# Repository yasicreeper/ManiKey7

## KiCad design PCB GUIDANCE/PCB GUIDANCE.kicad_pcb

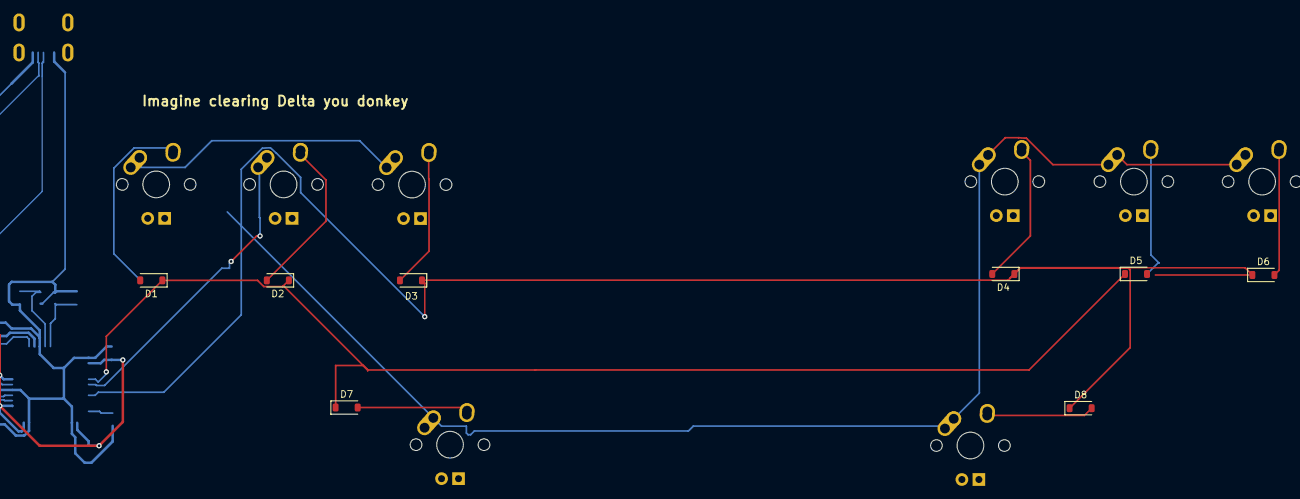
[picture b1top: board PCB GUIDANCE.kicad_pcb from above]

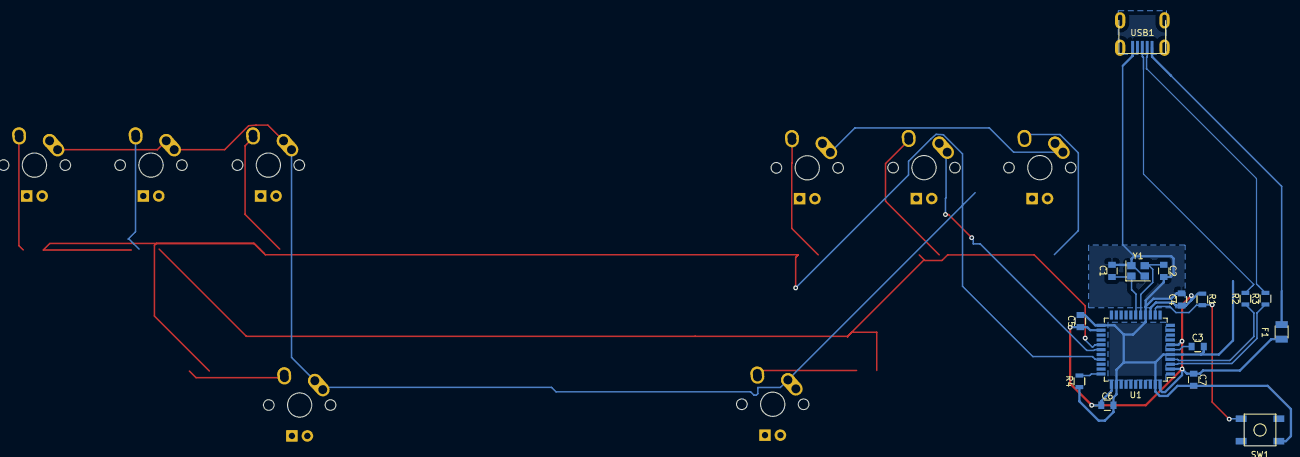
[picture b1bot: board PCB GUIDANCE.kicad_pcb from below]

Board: 2 copper layers, 32 parts (16 on the bottom side), 17 nets.

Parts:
C1, C2: 22pF; C_0805
C3: 1uF; C_0805
C4, C5, C6: 0.1uF; C_0805
C7: 10uF; C_0805
D1, D2, D3, D4, D5, D6, D7, D8: D_Small; D_SOD-123
F1: 500mA; Fuse_SMD1206_Reflow
MX1, MX2, MX3, MX4, MX5, MX6, MX7, MX8: MX-NoLED; MX-1U
R1, R4: 10k; R_0805
R2, R3: 22; R_0805
SW1: SW_Push; SKQG-1155865
U1: ATmega32U4-AU; TQFP-44_10x10mm_Pitch0.8mm
USB1: Molex-0548190589; Molex-0548190589-Assembly
Y1: Crystal_GND24_Small; Crystal_SMD_3225-4pin_3.2x2.5mm

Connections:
+5V: C4.1, C5.1, C6.1, C7.1, F1.1, R1.1, U1.2, U1.7, U1.14, U1.24, U1.34, U1.44
COL1: MX2.1 (COL), MX4.1 (COL), MX5.1 (COL), MX6.1 (COL), MX7.1 (COL), MX8.1 (COL), U1.28
COL2: MX1.1 (COL), MX3.1 (COL)
D+: R2.2, USB1.3
D-: R3.2, USB1.4
GND: C1.2, C2.2, C3.2, C4.2, C5.2, C6.2, C7.2, R4.1, SW1.1, U1.5, U1.15, U1.23, U1.35, U1.43, USB1.1, Y1.2, Y1.4
unnamed: D1.2 (A), MX1.2 (ROW)
unnamed: D2.2 (A), MX2.2 (ROW)
unnamed: D3.2 (A), MX3.2 (ROW)
unnamed: D4.2 (A), MX4.2 (ROW)
unnamed: D5.2 (A), MX5.2 (ROW)
unnamed: D6.2 (A), MX6.2 (ROW)
unnamed: D7.2 (A), MX7.2 (ROW)
unnamed: D8.2 (A), MX8.2 (ROW)
ROW0: D1.1 (K), D2.1 (K), D5.1 (K), D7.1 (K), U1.27
ROW1: D3.1 (K), D4.1 (K), D6.1 (K), D8.1 (K), U1.30
VCC: F1.2, USB1.5

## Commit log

2023-05-02 Add Submodules
2023-05-03 omg big updteate
